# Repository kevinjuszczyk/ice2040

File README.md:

# ICE2040
ICE40UP5K FPGA + RP2040 Hacker Board

## Overview
The ICE2040 combines a Lattice ICE40UP5K FPGA with a Raspberry Pi RP2040. The RP2040 is used to configure the ICE40 SRAM, and optionally provide a clock or host communication. Pmod connectors are provided for both the ICE40 and RP2040, with the rightmost connectors lined up in such a way that up to 16 additional lines between the ICE40 and RP2040 can be bridged together using a PCB or ribbon cable.

## Background
A friend expressed an interest in implementing a RISC-V processor using an FPGA, something like [learn-fpga](https://github.com/BrunoLevy/learn-fpga/blob/master/FemtoRV/TUTORIALS/FROM_BLINKER_TO_RISCV/README.md). Due to the ongoing parts shortage, many of the low-end FPGA dev boards are either out of stock, or have moved out of the pocket change price range. With an eye toward building a board using whatever might still be in stock, I found that the major retailers have many thousands of ICE40 parts in fine pitch BGA packages. I started playing around in KiCad with the ICE40UP5K-UWG30 (30-ball 0.4mm pitch) part to see if there was a way to fan out enough of the pins to make a reasonably useful board. By modifying the shape of the pads, I was able to achieve a complete fanout that can be fabricated with JLCPCB's 4-layer process. Most boards like this use an FTDI serial converter for host communication and FPGA configuration, but these have also been hard to get. I decided to use an RP2040 for these functions, since they are in stock and much less expensive. 

## Build
#### PCB
The board can be fabricated using [JLCPCB's](https://jlcpcb.com/) 4-layer process, and all components assembled (except for the ICE40 and Pmod headers) using their Economic PCBA service. [Jlcfab.zip](./kicad/jlcfab.zip) contains the fabrication files including the BOM, footprint position, drill, and Gerber files. [Jlcboardsettings.txt](./kicad/jlcboardsettings.txt) shows how to configure the JLCPCB order screen. Note that you want to specify the technical review (Confirm Production Files) for both the board fabrication and assembly. This will let JLCPCB adjust the board traces and parts orientation as needed.

NOTE: If you haven't soldered BGA packages before, this is *not* a good one to start with.
1. When the board arrives, check that the RP2040 is functioning correctly by plugging it into the USB port of your PC. A new removable drive should pop up with the volume name of RPI-RP2.
2. Unplug the board.
3. To hand-solder the ICE40, cover the pads of the ICE40 footprint with a thin layer of tacky flux. If too much flux is used, it will boil when heated and dislodge the balls from the package. 
4. Smear a thin layer of solder paste on a flat metal surface, and then press the ICE40 into it. The idea is to get some paste to stick to the balls so that when heat is applied, the paste will flow down and pool on the pads. 
5. Place the ICE40 on the board and line up the package inside the silkscreen while making sure it stays flat on the board. 
6. Reflow either with an oven or by using a hotplate underneath and a heat gun above. 
7. Check that all pins are connected by using the multimeter diode check. Connect the positive lead to board ground, and then touch each ICE40 Pmod pad with the negative lead. A good connection will show a voltage drop between 0.5 to 0.7 volts. Test for continuity between the power rails and ground to make sure they are not shorted. 
8. If you find an open connection, it may be possible to save the part. Dissolve some tacky flux with an equal amount of 99% isopropyl. Drip this mixture around the perimeter of the part so that it wicks underneath. Soak up any excess with a paper towel, and let the flux dry for several hours. Reflow again.

#### Software
1. Hold down the BOOTSEL button on the board while you plug the board into your PC. Once the RPI-RP2 drive pops up, you can release the button.
2. Download the latest release of [CircuitPython](https://circuitpython.org/board/raspberry_pi_pico/)
3. Copy the .UF2 file to the RPI-RP2 drive.
4. The ICE2040 will reboot and a drive labeled CIRCUITPY will pop up.
5. Copy the [top_bitmap.bin](./icecube2/multiblink/multiblink_Implmnt/sbt/outputs/bitmap/top_bitmap.bin) file to the CIRCUITPY drive. This is an ICE40 FPGA bitstream designed to blink several LEDs on the bottom center Pmod port (labeled 25B, 13B, etc.)
6. Copy the [code.py](./circuitpython/code.py) file to the CIRCUITPY drive, overwriting the existing file. This is a python script designed to upload the top_bitmap.bin file into the ICE40.
7. If you have an LED Pmod plugged into the bottom center Pmod port, you should now see several LEDs blinking at various rates. A multimeter can also be used to check for correct operation. Pins 13B or 25B change slowly enough to show the voltage alternate between 0 and 3.3 volts.
8. CircuitPython will automatically run the code.py script whenever a file on the CIRCUITPY drive is changed (including top_bitmap.bin). A serial port is also provided for communication with the host PC. See the CircuitPython [documentation](https://learn.adafruit.com/welcome-to-circuitpython) for details.

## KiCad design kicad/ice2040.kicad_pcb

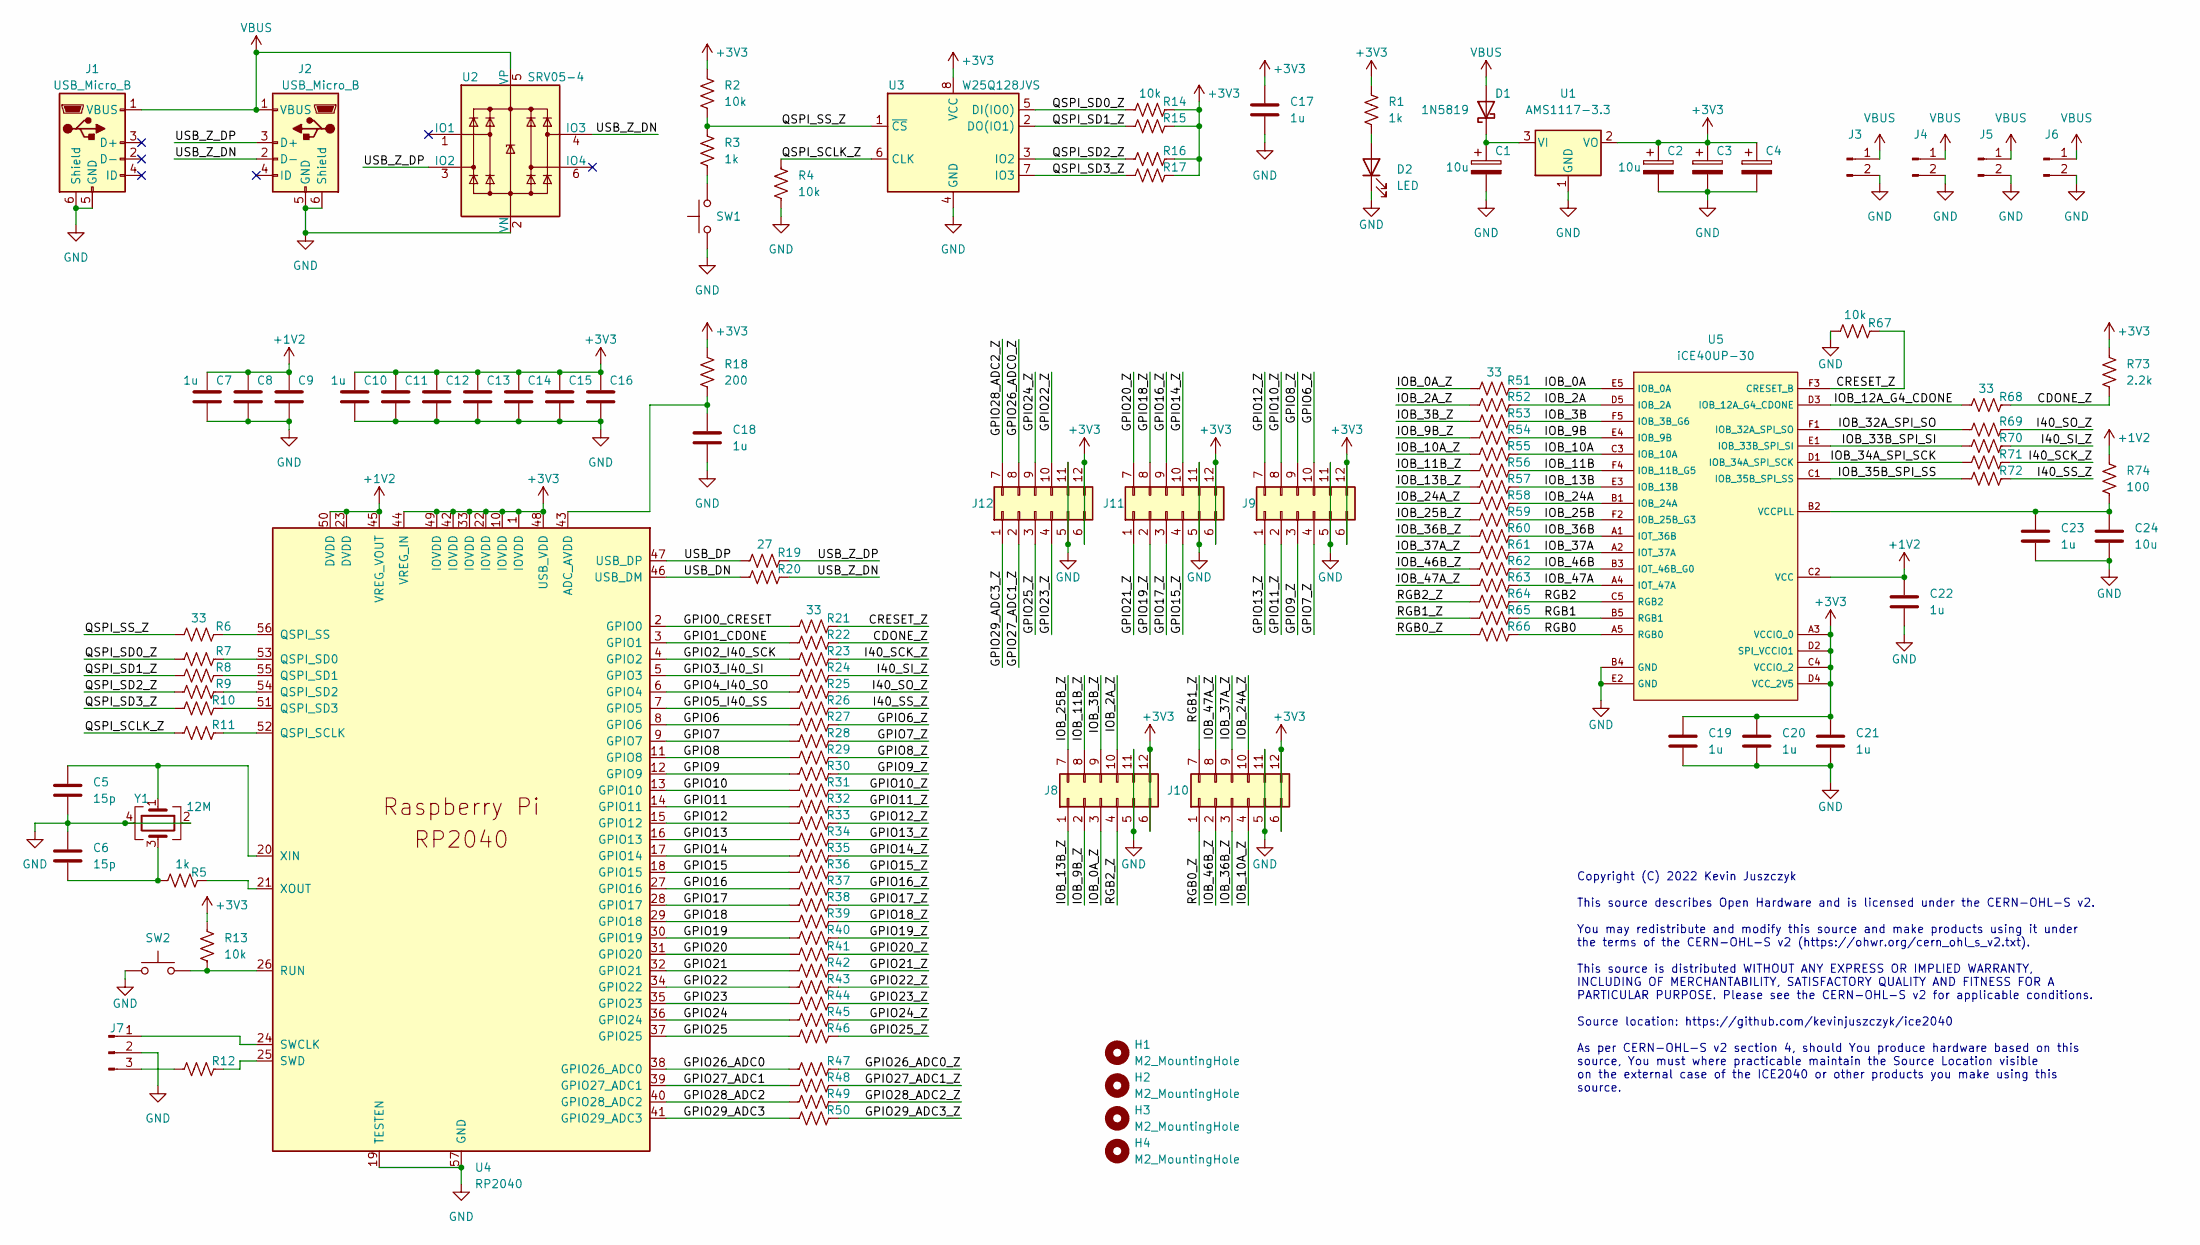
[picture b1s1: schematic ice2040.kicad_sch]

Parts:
C1, C2, C3, C4: 10u; CP_EIA-3216-18_Kemet-A; LCSC C7171
C5, C6: 15p; C_0402_1005Metric; LCSC C1548
C7, C8, C9, C10, C11, C12, C13, C14, C15, C16, C17, C18, C19, C20, C21, C22, C23: 1u; C_0402_1005Metric; LCSC C52923
C24: 10u; C_0402_1005Metric; LCSC C15525
D1: 1N5819; D_SOD-123; LCSC C8598
D2: LED; D_0603_1608Metric; LCSC C2286
H1, H2, H3, H4: M2_MountingHole; MountingHole_2.2mm_M2_ISO7380
J1, J2: USB_Micro_B; USB_Micro-B_Molex-105017-0001; LCSC C136000
J3, J4, J5, J6: 1x02_P2.54; PinHeader_1x02_P2.54mm_Vertical
J7: 1x03_P2.54; PinHeader_1x03_P2.54mm_Vertical
J8, J9, J10, J11, J12: PMOD_HOST
R1, R3, R5: 1k; R_0402_1005Metric; LCSC C11702
R2, R4, R13, R14, R15, R16, R17, R67: 10k; R_0402_1005Metric; LCSC C25744
R6, R7, R8, R9, R10, R11, R12, R21, R22, R23, R24, R25, R26, R27, R28, R29, R30, R31, R32, R33, R34, R35, R36, R37, R38, R39, R40, R41, R42, R43, R44, R45, R46, R47, R48, R49, R50, R51, R52, R53, R54, R55, R56, R57, R58, R59, R60, R61, R62, R63, R64, R65, R66, R68, R69, R70, R71, R72: 33; R_0402_1005Metric; LCSC C25105
R18: 200; R_0402_1005Metric; LCSC C25087
R19, R20: 27; R_0603_1608Metric; LCSC C25190
R73: 2.2k; R_0402_1005Metric; LCSC C25879
R74: 100; R_0402_1005Metric; LCSC C25076
SW1, SW2: SW_Push; SW_SPST_SKQG_WithoutStem; LCSC C318884
U1: AMS1117-3.3; SOT-223-3_TabPin2; LCSC C6186
U2: SRV05-4; SOT-23-6; LCSC C85364
U3: W25Q128JVS; SOIC-8_5.23x5.23mm_P1.27mm; LCSC C97521
U4: RP2040; QFN-56-1EP_7x7mm_P0.4mm_EP3.2x3.2mm_MoreThermalVias; LCSC C2040
U5: iCE40UP-30; BGA-30_5x6_2.114x2.537mm; LCSC C1519053
Y1: 12M; Crystal_SMD_SeikoEpson_FA238-4Pin_3.2x2.5mm; LCSC C9002

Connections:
+1V2: C7.1, C8.1, C9.1, C22.1, R74.2, U4.23 (DVDD), U4.45 (VREG_VOUT), U4.50 (DVDD), U5.C2 (VCC)
+3V3: C2.1, C3.1, C4.1, C10.1, C11.1, C12.1, C13.1, C14.1, C15.1, C16.1, C17.1, C19.1, C20.1, C21.1, J8.6, J8.12, J9.6, J9.12, J10.6, J10.12, J11.6, J11.12, J12.6, J12.12, R1.2, R2.2, R13.2, R14.1, R15.1, R16.1, R17.1, R18.2, R73.2, U1.2 (VO), U3.8 (VCC), U4.1 (IOVDD), U4.10 (IOVDD), U4.22 (IOVDD), U4.33 (IOVDD), U4.42 (IOVDD), U4.44 (VREG_IN), U4.48 (USB_VDD), U4.49 (IOVDD), U5.A3 (VCCIO_0), U5.C4 (VCCIO_2), U5.D2 (SPI_VCCIO1), U5.D4 (VCC_2V5)
/CDONE_Z: R22.1, R68.1, R73.1
/CRESET_Z: R21.1, R67.1, U5.F3 (CRESET_B)
/GPIO0_CRESET: R21.2, U4.2 (GPIO0)
/GPIO1_CDONE: R22.2, U4.3 (GPIO1)
/GPIO2_I40_SCK: R23.2, U4.4 (GPIO2)
/GPIO3_I40_SI: R24.2, U4.5 (GPIO3)
/GPIO4_I40_SO: R25.2, U4.6 (GPIO4)
/GPIO5_I40_SS: R26.2, U4.7 (GPIO5)
/GPIO6: R27.2, U4.8 (GPIO6)
/GPIO6_Z: J9.10, R27.1
/GPIO7: R28.2, U4.9 (GPIO7)
/GPIO7_Z: J9.4, R28.1
/GPIO8: R29.2, U4.11 (GPIO8)
/GPIO8_Z: J9.9, R29.1
/GPIO9: R30.2, U4.12 (GPIO9)
/GPIO9_Z: J9.3, R30.1
/GPIO10: R31.2, U4.13 (GPIO10)
/GPIO10_Z: J9.8, R31.1
/GPIO11: R32.2, U4.14 (GPIO11)
/GPIO11_Z: J9.2, R32.1
/GPIO12: R33.2, U4.15 (GPIO12)
/GPIO12_Z: J9.7, R33.1
/GPIO13: R34.2, U4.16 (GPIO13)
/GPIO13_Z: J9.1, R34.1
/GPIO14: R35.2, U4.17 (GPIO14)
/GPIO14_Z: J11.10, R35.1
/GPIO15: R36.2, U4.18 (GPIO15)
/GPIO15_Z: J11.4, R36.1
/GPIO16: R37.2, U4.27 (GPIO16)
/GPIO16_Z: J11.9, R37.1
/GPIO17: R38.2, U4.28 (GPIO17)
/GPIO17_Z: J11.3, R38.1
/GPIO18: R39.2, U4.29 (GPIO18)
/GPIO18_Z: J11.8, R39.1
/GPIO19: R40.2, U4.30 (GPIO19)
/GPIO19_Z: J11.2, R40.1
/GPIO20: R41.2, U4.31 (GPIO20)
/GPIO20_Z: J11.7, R41.1
/GPIO21: R42.2, U4.32 (GPIO21)
/GPIO21_Z: J11.1, R42.1
/GPIO22: R43.2, U4.34 (GPIO22)
/GPIO22_Z: J12.10, R43.1
/GPIO23: R44.2, U4.35 (GPIO23)
/GPIO23_Z: J12.4, R44.1
/GPIO24: R45.2, U4.36 (GPIO24)
/GPIO24_Z: J12.9, R45.1
/GPIO25: R46.2, U4.37 (GPIO25)
/GPIO25_Z: J12.3, R46.1
/GPIO26_ADC0: R47.2, U4.38 (GPIO26_ADC0)
/GPIO26_ADC0_Z: J12.8, R47.1
/GPIO27_ADC1: R48.2, U4.39 (GPIO27_ADC1)
/GPIO27_ADC1_Z: J12.2, R48.1
/GPIO28_ADC2: R49.2, U4.40 (GPIO28_ADC2)
/GPIO28_ADC2_Z: J12.7, R49.1
/GPIO29_ADC3: R50.2, U4.41 (GPIO29_ADC3)
/GPIO29_ADC3_Z: J12.1, R50.1
/I40_SCK_Z: R23.1, R71.1
/I40_SI_Z: R24.1, R70.1
/I40_SO_Z: R25.1, R69.1
/I40_SS_Z: R26.1, R72.1
/IOB_0A: R51.1, U5.E5 (IOB_0A)
/IOB_0A_Z: J8.3, R51.2
/IOB_2A: R52.1, U5.D5 (IOB_2A)
/IOB_2A_Z: J8.10, R52.2
/IOB_3B: R53.1, U5.F5 (IOB_3B_G6)
/IOB_3B_Z: J8.9, R53.2
/IOB_9B: R54.1, U5.E4 (IOB_9B)
/IOB_9B_Z: J8.2, R54.2
/IOB_10A: R55.1, U5.C3 (IOB_10A)
/IOB_10A_Z: J10.4, R55.2
/IOB_11B: R56.1, U5.F4 (IOB_11B_G5)
/IOB_11B_Z: J8.8, R56.2
/IOB_12A_G4_CDONE: R68.2, U5.D3 (IOB_12A_G4_CDONE)
/IOB_13B: R57.1, U5.E3 (IOB_13B)
/IOB_13B_Z: J8.1, R57.2
/IOB_24A: R58.1, U5.B1 (IOB_24A)
/IOB_24A_Z: J10.10, R58.2
/IOB_25B: R59.1, U5.F2 (IOB_25B_G3)
/IOB_25B_Z: J8.7, R59.2
/IOB_32A_SPI_SO: R69.2, U5.F1 (IOB_32A_SPI_SO)
/IOB_33B_SPI_SI: R70.2, U5.E1 (IOB_33B_SPI_SI)
/IOB_34A_SPI_SCK: R71.2, U5.D1 (IOB_34A_SPI_SCK)
/IOB_35B_SPI_SS: R72.2, U5.C1 (IOB_35B_SPI_SS)
/IOB_36B: R60.1, U5.A1 (IOT_36B)
/IOB_36B_Z: J10.3, R60.2
/IOB_37A: R61.1, U5.A2 (IOT_37A)
/IOB_37A_Z: J10.9, R61.2
/IOB_46B: R62.1, U5.B3 (IOT_46B_G0)
/IOB_46B_Z: J10.2, R62.2
/IOB_47A: R63.1, U5.A4 (IOT_47A)
/IOB_47A_Z: J10.8, R63.2
/QSPI_SCLK_Z: R4.2, R11.2, U3.6 (CLK)
/QSPI_SD0_Z: R7.2, R14.2, U3.5 (DI(IO0))
/QSPI_SD1_Z: R8.2, R15.2, U3.2 (DO(IO1))
/QSPI_SD2_Z: R9.2, R16.2, U3.3 (IO2)
/QSPI_SD3_Z: R10.2, R17.2, U3.7 (IO3)
/QSPI_SS_Z: R2.1, R3.2, R6.2, U3.1 (~CS)
/RGB0: R66.1, U5.A5 (RGB0)
/RGB0_Z: J10.1, R66.2
/RGB1: R65.1, U5.B5 (RGB1)
/RGB1_Z: J10.7, R65.2
/RGB2: R64.1, U5.C5 (RGB2)
/RGB2_Z: J8.4, R64.2
/USB_DN: R20.2, U4.46 (USB_DM)
/USB_DP: R19.2, U4.47 (USB_DP)
/USB_Z_DN: J2.2 (D-), R20.1, U2.4 (IO3)
/USB_Z_DP: J2.3 (D+), R19.1, U2.3 (IO2)
GND: C1.2, C2.2, C3.2, C4.2, C5.2, C6.1, C7.2, C8.2, C9.2, C10.2, C11.2, C12.2, C13.2, C14.2, C15.2, C16.2, C17.2, C18.2, C19.2, C20.2, C21.2, C22.2, C23.2, C24.2, D2.1 (K), J1.5 (GND), J1.6 (Shield), J2.5 (GND), J2.6 (Shield), J3.2, J4.2, J5.2, J6.2, J7.2, J8.5, J8.11, J9.5, J9.11, J10.5, J10.11, J11.5, J11.11, J12.5, J12.11, R4.1, R67.2, SW1.1, SW2.1, U1.1 (GND), U2.2 (VN), U3.4 (GND), U4.19 (TESTEN), U4.57 (GND), U5.B4 (GND), U5.E2 (GND), Y1.2, Y1.4
unnamed: C1.1, D1.1 (K), U1.3 (VI)
unnamed: C5.1, U4.20 (XIN), Y1.1
unnamed: C6.2, R5.2, Y1.3
unnamed: C18.1, R18.1, U4.43 (ADC_AVDD)
unnamed: C23.1, C24.1, R74.1, U5.B2 (VCCPLL)
unnamed: D2.2 (A), R1.1
unnamed: J7.1, U4.24 (SWCLK)
unnamed: J7.3, R12.2
unnamed: R3.1, SW1.2
unnamed: R5.1, U4.21 (XOUT)
unnamed: R6.1, U4.56 (QSPI_SS)
unnamed: R7.1, U4.53 (QSPI_SD0)
unnamed: R8.1, U4.55 (QSPI_SD1)
unnamed: R9.1, U4.54 (QSPI_SD2)
unnamed: R10.1, U4.51 (QSPI_SD3)
unnamed: R11.1, U4.52 (QSPI_SCLK)
unnamed: R12.1, U4.25 (SWD)
unnamed: R13.1, SW2.2, U4.26 (RUN)
VBUS: D1.2 (A), J1.1 (VBUS), J2.1 (VBUS), J3.1, J4.1, J5.1, J6.1, U2.5 (VP)

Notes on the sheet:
Copyright (C) 2022 Kevin Juszczyk This source describes Open Hardware and is licensed under the CERN-OHL-S v2. You may redistribute and modify this source and make products using it under the terms of the CERN-OHL-S v2 (https://ohwr.org/cern_ohl_s_v2.txt). This source is distributed WITHOUT ANY EXP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

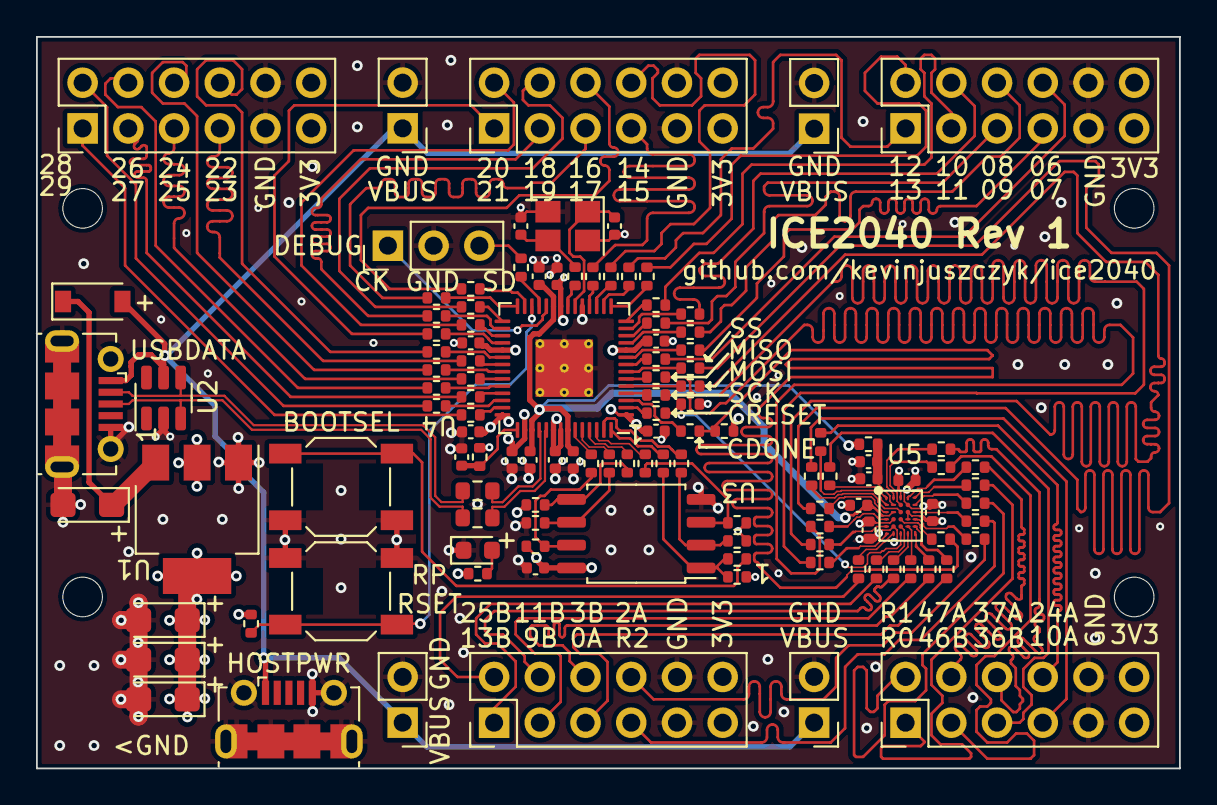
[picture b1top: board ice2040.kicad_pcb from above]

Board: 4 copper layers, 63.5 x 40.6 mm, 124 parts (0 on the bottom side), 129 nets.

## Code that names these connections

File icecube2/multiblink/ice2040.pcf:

set_io IOB_0A  E5
set_io IOB_2A  D5
set_io IOB_3B  F5
set_io IOB_9B  E4
set_io IOB_10A C3
set_io IOB_11B F4
set_io IOB_13B E3
set_io IOB_24A B1
set_io IOB_25B F2
set_io IOB_36B A1
set_io IOB_37A A2
set_io IOB_46B B3
set_io IOB_47A A4
set_io RGB2 C5
set_io RGB1 B5
set_io RGB0 A5

set_io IOB_12A_G4_CDONE D3
set_io IOB_32A_SPI_SO F1
set_io IOB_33B_SPI_SI E1
set_io IOB_34A_SPI_SCK D1
set_io IOB_35B_SPI_SS C1

set_io P1A1  E3
set_io P1A2  E4
set_io P1A3  E5
set_io P1A4  C5
set_io P1A7  F2
set_io P1A8  F4
set_io P1A9  F5
set_io P1A10 D5

set_io P1B1       A5
set_io P1B2       B3
set_io P1B3       A1
set_io P1B4       C3
set_io P1B7       B5
set_io P1B8       A4
set_io P1B9       A2
set_io P1B10      B1

set_io CLK        D3
set_frequency CLK 12

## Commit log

2022-09-30 footprint pic

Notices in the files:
kicad/ice2040.kicad_pcb:
As per CERN-OHL-S v2 section 4, should You produce hardware based on this
